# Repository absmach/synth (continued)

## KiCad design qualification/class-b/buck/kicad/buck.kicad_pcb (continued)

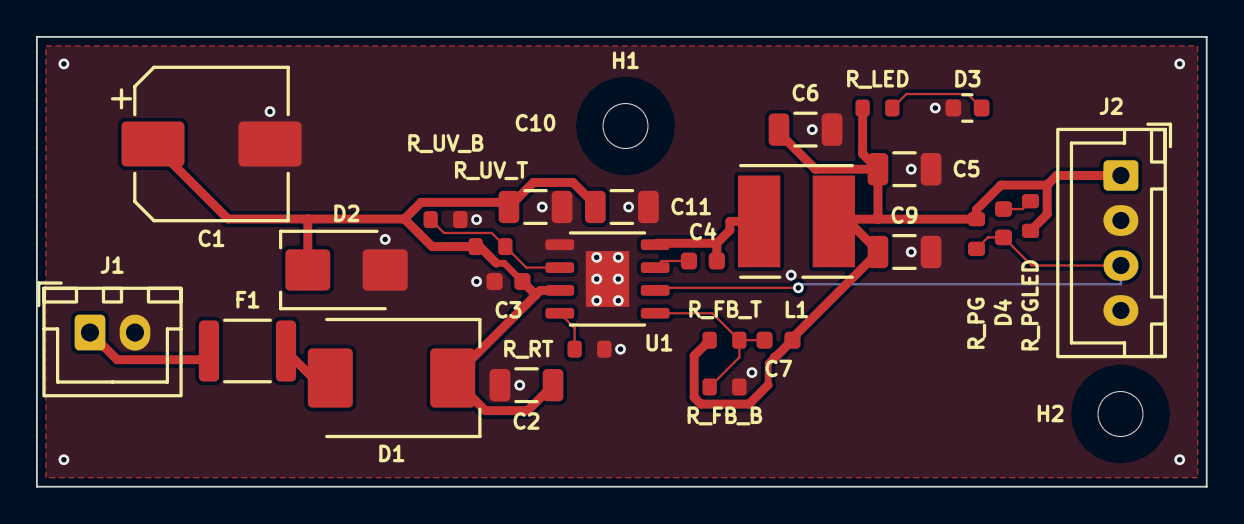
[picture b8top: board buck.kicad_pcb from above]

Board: 4 copper layers, 65.0 x 25.0 mm, 29 parts (0 on the bottom side), 13 nets.

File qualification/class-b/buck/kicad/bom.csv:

refdes,value,kind,description,kicad_symbol,kicad_footprint,lcsc_pn,mpn
C1,47uF,capacitor,"Honor Elec RVT1H470M0810, 47 uF 50 V +/-20 % 105 C SMD aluminium electrolytic, 8 mm diameter x 10.2 mm, polarised (pin 1 is +); JLCPCB C2895739",Device:C_Polarized,Capacitor_SMD:CP_Elec_8x10,,RVT1H470M0810
C10,10uF,capacitor,"Samsung CL31B106KBHNNNE, 10 uF +/-10 % 50 V X7R 1206 MLCC, -55 to 125 C (distributor listing); JLCPCB C89632",Device:C,Capacitor_SMD:C_1206_3216Metric,C89632,CL31B106KBHNNNE
C11,10uF,capacitor,"Samsung CL31B106KBHNNNE, 10 uF +/-10 % 50 V X7R 1206 MLCC, -55 to 125 C (distributor listing); JLCPCB C89632",Device:C,Capacitor_SMD:C_1206_3216Metric,C89632,CL31B106KBHNNNE
C2,10uF,capacitor,"Samsung CL31B106KBHNNNE, 10 uF +/-10 % 50 V X7R 1206 MLCC, -55 to 125 C (distributor listing); JLCPCB C89632",Device:C,Capacitor_SMD:C_1206_3216Metric,C89632,CL31B106KBHNNNE
C3,220nF,capacitor,"Generic 0603 MLCC, X7R/X5R, any value",Device:C,Capacitor_SMD:C_0603_1608Metric,,
C4,100nF,capacitor,"Generic 0603 MLCC, X7R/X5R, any value",Device:C,Capacitor_SMD:C_0603_1608Metric,,
C5,22uF,capacitor,"Samsung CL31A226KAHNNNE, 22 uF +/-10 % 25 V X5R 1206 MLCC, 1.60 mm max thickness, -55 to 85 C, +/-15 % over temperature; JLCPCB C12891",Device:C,Capacitor_SMD:C_1206_3216Metric,C12891,CL31A226KAHNNNE
C6,22uF,capacitor,"Samsung CL31A226KAHNNNE, 22 uF +/-10 % 25 V X5R 1206 MLCC, 1.60 mm max thickness, -55 to 85 C, +/-15 % over temperature; JLCPCB C12891",Device:C,Capacitor_SMD:C_1206_3216Metric,C12891,CL31A226KAHNNNE
C7,56pF,capacitor,"Generic 0603 MLCC, X7R/X5R, any value",Device:C,Capacitor_SMD:C_0603_1608Metric,,
C9,22uF,capacitor,"Samsung CL31A226KAHNNNE, 22 uF +/-10 % 25 V X5R 1206 MLCC, 1.60 mm max thickness, -55 to 85 C, +/-15 % over temperature; JLCPCB C12891",Device:C,Capacitor_SMD:C_1206_3216Metric,C12891,CL31A226KAHNNNE
D1,SS36,diode,"Vishay SS36 60 V 3 A Schottky rectifier, SMC (DO-214AB), for reverse-polarity blocking",Device:D_Schottky,Diode_SMD:D_SMC,,SS36
D2,SMBJ30A,diode,"Vishay SMBJ30A 600 W unidirectional TVS, SMB (DO-214AA). max_voltage_v is the 30 V standoff VWM, not a clamp or abs max: VBR 33.3-36.8 V at 1 mA, VC 48.4 V at 12.4 A",Device:D_Zener,Diode_SMD:D_SMB,,SMBJ30A
D3,PWR,led,"Lite-On LTST-C190KGKT green AlInGaP LED, 0603, Vf 1.9 to 2.4V at 20mA",Device:LED,LED_SMD:LED_0603_1608Metric,,LTST-C190KGKT
D4,PG FAULT,led,"Lite-On LTST-C190KGKT green AlInGaP LED, 0603, Vf 1.9 to 2.4V at 20mA",Device:LED,LED_SMD:LED_0603_1608Metric,,LTST-C190KGKT
F1,1.1A_PTC,fuse,"Bourns MF-MSMF110/33X resettable PTC fuse, 1812. max_current_ma is Ihold 1.1 A at 23 C (0.63 A at 70 C, 0.50 A at 85 C); Itrip 2.2 A, Vmax 33 V",Device:Polyfuse,Fuse:Fuse_1812_4532Metric,,MF-MSMF110/33X
H1,M2.5,mounting_hole,M2.5 non-plated mounting hole (NPTH) for a board corner,Mechanical:MountingHole,MountingHole:MountingHole_2.5mm,,
H2,M2.5,mounting_hole,M2.5 non-plated mounting hole (NPTH) for a board corner,Mechanical:MountingHole,MountingHole:MountingHole_2.5mm,,
J1,24V_IN,connector,"JST XH 2.5 mm pitch 2-pin vertical header B2B-XH-A, 250 V / 3 A per JST XH sheet",Connector_Generic:Conn_01x02,Connector_JST:JST_XH_B2B-XH-A_1x02_P2.50mm_Vertical,,B2B-XH-A
J2,3V3_OUT,connector,"JST XH 2.5 mm pitch 4-pin vertical header B4B-XH-A, 250 V / 3 A per JST XH sheet",Connector_Generic:Conn_01x04,Connector_JST:JST_XH_B4B-XH-A_1x04_P2.50mm_Vertical,,B4B-XH-A
L1,6.8uH,inductor,"Bourns SRN6045TA-6R8M 6.8 uH semi-shielded power inductor, 6.0 x 6.0 mm. Datasheet typ: Isat 5.7 A (L drops 30%), Irms 3.6 A (max_current_ma is Irms), DCR 34 mOhm +-20%",Device:L,Inductor_SMD:L_Bourns_SRN6045TA,,SRN6045TA-6R8M
R_FB_B,43.2k,resistor,"Generic 0603 thick-film resistor, any value",Device:R_US,Resistor_SMD:R_0603_1608Metric,,
R_FB_T,100k,resistor,"Generic 0603 thick-film resistor, any value",Device:R_US,Resistor_SMD:R_0603_1608Metric,,
R_LED,470,resistor,"Generic 0603 thick-film resistor, any value",Device:R_US,Resistor_SMD:R_0603_1608Metric,,
R_PG,100k,resistor,"Generic 0603 thick-film resistor, any value",Device:R_US,Resistor_SMD:R_0603_1608Metric,,
R_PGLED,470,resistor,"Generic 0603 thick-film resistor, any value",Device:R_US,Resistor_SMD:R_0603_1608Metric,,
R_RT,33k,resistor,"Generic 0603 thick-film resistor, any value",Device:R_US,Resistor_SMD:R_0603_1608Metric,,
R_UV_B,100k,resistor,"Generic 0603 thick-film resistor, any value",Device:R_US,Resistor_SMD:R_0603_1608Metric,,
R_UV_T,1.37M,resistor,"Generic 0603 thick-film resistor, any value",Device:R_US,Resistor_SMD:R_0603_1608Metric,,
U1,LMR38010SDDAR,regulator,"TI LMR38010SDDAR 4.2-80 V input, 1 A synchronous step-down converter, adjustable 400 kHz-2.2 MHz through RT, PFM with spread spectrum, HSOIC-8 (DDA) with exposed thermal pad and open-drain power-good. VFB 1.0 V; VIN abs max 85 V",,Package_SO:HSOP-8-1EP_3.9x4.9mm_P1.27mm_EP2.41x3.1mm,,LMR38010SDDAR
